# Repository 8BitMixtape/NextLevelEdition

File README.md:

NextLevelEdition
================

SMD 32U4 Massproduction Ready PCB that fits in Mixtape

How to install
================
Download Hardware Cores from Sparkfun:
https://learn.sparkfun.com/tutorials/pro-micro--fio-v3-hookup-guide/installing-mac--linux

For Linux udev rules needs to be changed:
http://forum.arduino.cc/index.php?topic=217910.0

```
/etc/udev/rules.d/70-persistent-net.rules

 # 8Bit Mixtape NextLevel Shit
 
ATTRS{idVendor}=="1b4f", ATTRS{idProduct}=="f100", ENV{ID_MM_DEVICE_IGNORE}="1"

ATTRS{idVendor}=="1b4f", ATTRS{idProduct}=="f101", ENV{ID_MM_DEVICE_IGNORE}="1"
```

Troubleshooting
================

If the serial port doesn't appear, see above.

Strange blinking: Did you attach the LiPo battery?

Bricked the board? if you choose the wrong board and upload this might happen. solder on the ISP plug and burn the bootloader. the files is in the core.

for linux:
`avrdude -P /dev/ttyACM0 -b 19200 -c avrisp -p m32u4 -v -e -U flash:w:Caterina-fio.hex:i`

Pins:
================

2 x Analog Input
----------------
A0 ( you can also only write 0) -> D18

A1 ( you can also only write 1) -> D19

2 x Digital Input / Buttons
---------------------------
D2 (2)

D3 (3)

Sound Output
------------
D9 (9) also connected to LED2

LEDs
----
D13 (13)

the middle i don't know. maybe charge state?

RX (0)

TX (1)

Timers
============

To change the prescaler of the timer connected to Pin9 (sound output)

```
TCCR1B = TCCR0B & 0b11111001; //no timer pre-scaler, fast PWM
```

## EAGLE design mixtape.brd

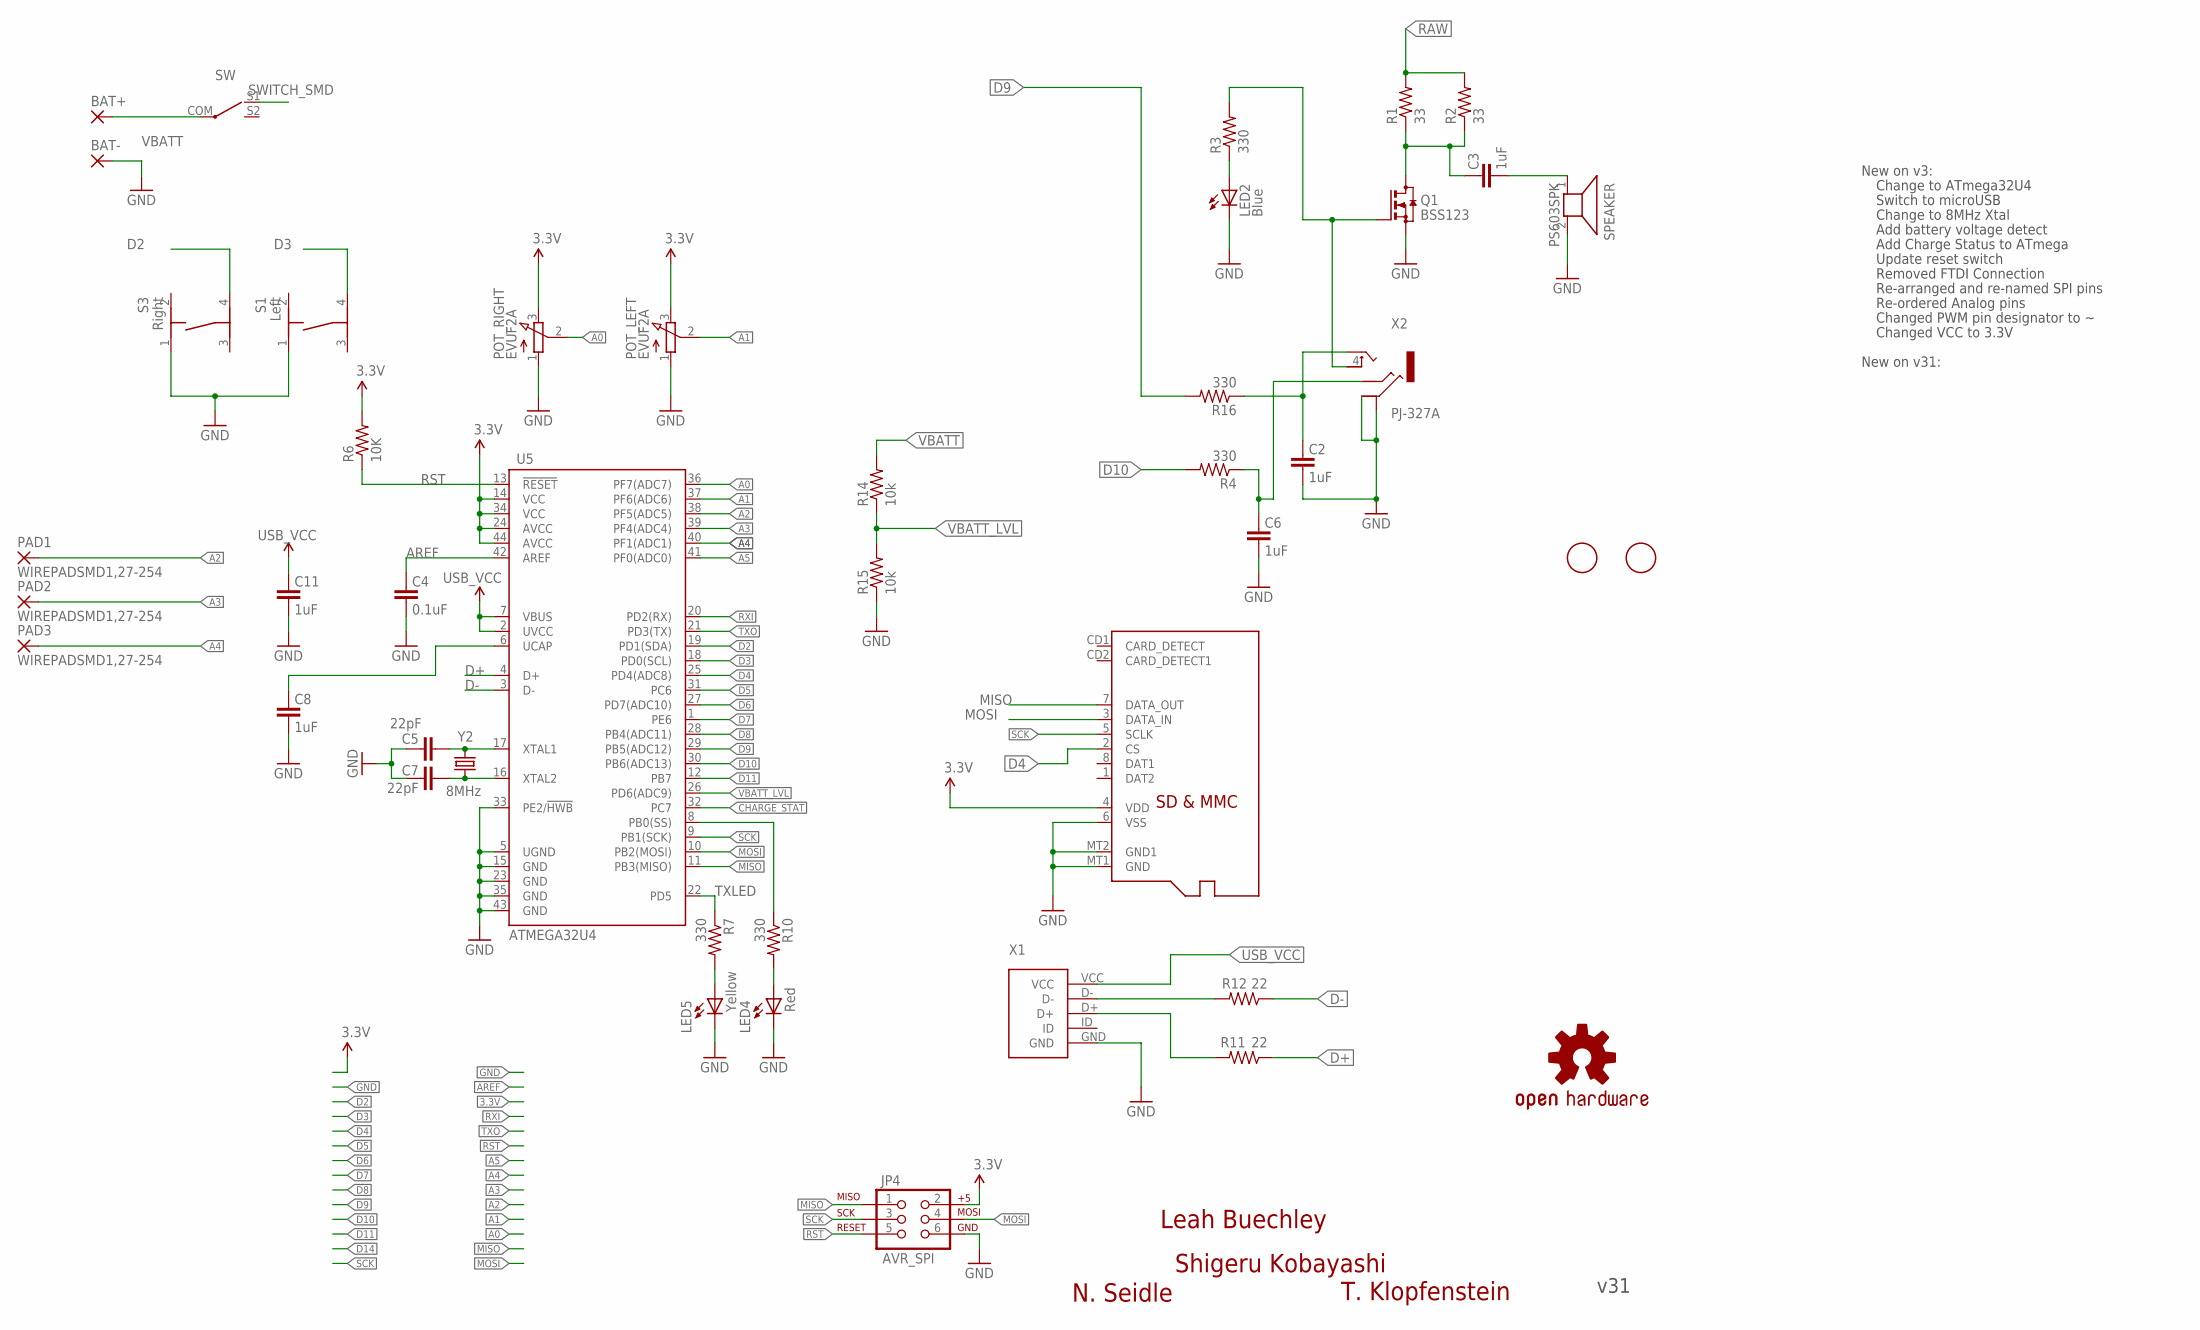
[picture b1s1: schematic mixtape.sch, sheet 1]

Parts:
BAT+: SMD5; SMD2,54-5,08
BAT-: SMD5; SMD2,54-5,08
C2, C3, C6, C8, C11: 1uF; 0603-CAP
C4: 0.1uF; 0603-CAP
C5, C7: 22pF; 0603-CAP
JP4: AVR_SPI; 2X3
LED2: Blue; LED-0603
LED4: Red; LED-0603
LED5: Yellow; LED-0603
LOGO1: OSHW-LOGOL; OSHW-LOGO-L
PAD1, PAD2, PAD3: WIREPADSMD1,27-254; SMD1,27-2,54
POT_LEFT: EVUF2A; EVUF
POT_RIGHT: EVUF2A; EVUF
Q1: BSS123; SOT23
R1, R2: 33; 0603-RES
R3, R4, R7, R10, R16: 330; 0603-RES
R6: 10K; 0603-RES
R11, R12: 22; 0603-RES
R14, R15: 10k; 0603-RES
S1: Left; TASTER-9314_SMD
S3: Right; TASTER-9314_SMD
SD: MICROSD
SPEAKER: PS603SPK; PS603
SW: SWITCH_SMD
U5: ATMEGA32U4; QFN-44-NOPAD_1:1
U$1, U$2: FIDUCIAL; FIDUCIAL_1MM
X1: USB_B_SMD
X2: PJ-327A
Y2: 8MHz; CRYSTAL-SMD-5X3

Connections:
3.3V: JP4.2, POT_LEFT.3 (E), POT_RIGHT.3 (E), R6.2, SD.4 (VDD), U5.14 (VCC), U5.24 (AVCC), U5.34 (VCC), U5.44 (AVCC); also elsewhere on the board
A0: POT_RIGHT.2 (S), U5.36 (PF7(ADC7))
A1: POT_LEFT.2 (S), U5.37 (PF6(ADC6))
A2: PAD1.1, U5.38 (PF5(ADC5))
A3: PAD2.1, U5.39 (PF4(ADC4))
A4: PAD3.1, U5.40 (PF1(ADC1))
A5: U5.41 (PF0(ADC0))
AREF: C4.2, U5.42 (AREF)
CHARGE_STAT: U5.32 (PC7); also elsewhere on the board
D2: S3.4, U5.19 (PD1(SDA))
D3: S1.4, U5.18 (PD0(SCL))
D4: SD.2 (CS), U5.25 (PD4(ADC8))
D5: U5.31 (PC6)
D6: U5.27 (PD7(ADC10))
D7: U5.1 (PE6)
D8: U5.28 (PB4(ADC11))
D9: R16.2, U5.29 (PB5(ADC12))
D10: R4.2, U5.30 (PB6(ADC13))
D11: U5.12 (PB7)
D14: R10.1, U5.8 (PB0(SS))
D+: R11.1, U5.4 (D+)
D-: R12.1, U5.3 (D-)
GND: BAT-.1, C2.1, C4.1, C5.2, C6.1, C7.2, C8.1, C11.1, JP4.6, LED2.C, LED4.C, LED5.C, POT_LEFT.1 (A), POT_RIGHT.1 (A), Q1.2 (S), R15.1, S1.1, S3.1, SD.6 (VSS), SD.MT1 (GND), SD.MT2 (GND1), SPEAKER.2, U5.5 (UGND), U5.15 (GND), U5.23 (GND), U5.33 (PE2/!HWB), U5.35 (GND), U5.43 (GND), X1.GND, X2.1, X2.5; also elsewhere on the board
MISO: JP4.1, SD.7 (DATA_OUT), U5.11 (PB3(MISO))
MOSI: JP4.4, SD.3 (DATA_IN), U5.10 (PB2(MOSI))
unnamed: C3.2, Q1.3 (D), R1.1, R2.1
unnamed: C3.1, SPEAKER.1
unnamed: C6.2, R4.1, X2.3
unnamed: R11.2, X1.D+
unnamed: LED2.A, R3.1
unnamed: Q1.1 (G), R3.2, X2.4
unnamed: LED5.A, R7.2
unnamed: C7.1, U5.16 (XTAL2), Y2.1
unnamed: C5.1, U5.17 (XTAL1), Y2.3 (2)
unnamed: LED4.A, R10.2
unnamed: R12.2, X1.D-
unnamed: C2.2, R16.1, X2.2
RAW: R1.2, R2.2, SW.S1; also elsewhere on the board
RST: JP4.5, R6.1, U5.13 (!RESET)
RXI: U5.20 (PD2(RX))
SCK: JP4.3, SD.5 (SCLK), U5.9 (PB1(SCK))
TXLED: R7.1, U5.22 (PD5)
TXO: U5.21 (PD3(TX))
UCAP: C8.2, U5.6 (UCAP)
USB_VCC: C11.2, U5.2 (UVCC), U5.7 (VBUS), X1.VCC; also elsewhere on the board
VBATT: BAT+.1, R14.2, SW.COM; also elsewhere on the board
VBATT_LVL: R14.1, R15.2, U5.26 (PD6(ADC9))

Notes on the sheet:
Shigeru Kobayashi
Change to ATmega32U4
Switch to microUSB
New on v3:
Change to 8MHz Xtal
Add battery voltage detect
Add Charge Status to ATmega
Update reset switch
Removed FTDI Connection
Re-arranged and re-named SPI pins
Re-ordered Analog pins
Changed PWM pin designator to ~
Changed VCC to 3.3V
New on v31:
v31
N. Seidle
T. Klopfenstein
Leah Buechley

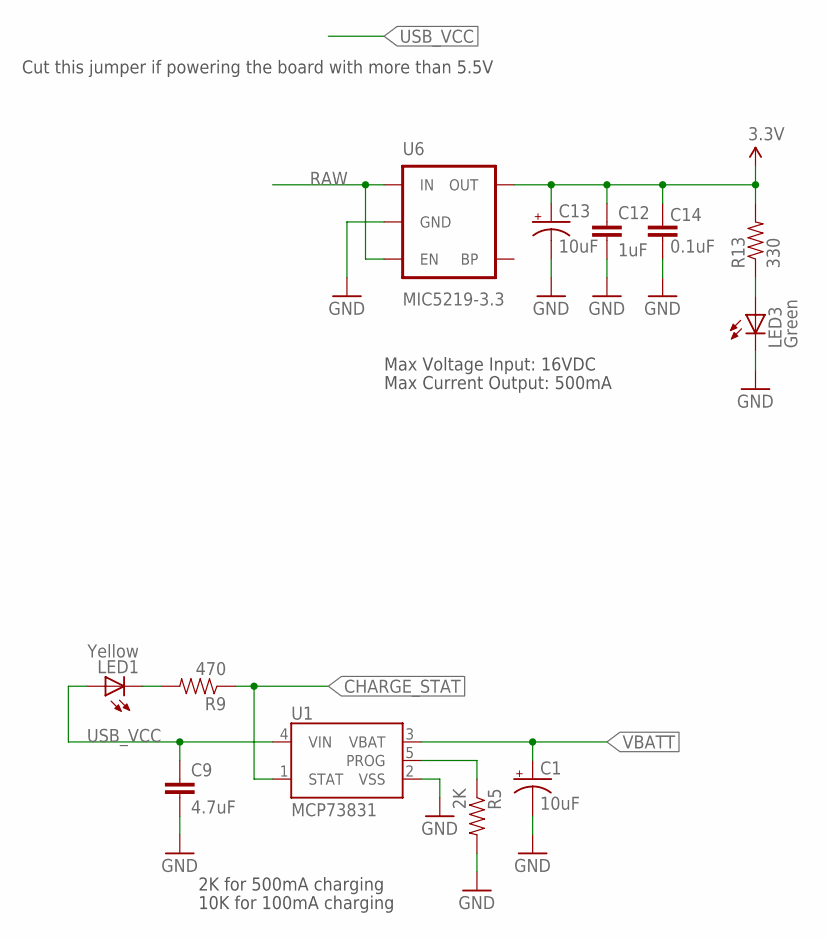
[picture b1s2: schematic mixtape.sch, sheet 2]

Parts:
C1, C13: 10uF; EIA3216
C9: 4.7uF; 0603-CAP
C12: 1uF; 0603-CAP
C14: 0.1uF; 0603-CAP
LED1: Yellow; LED-0603
LED3: Green; LED-0603
R5: 2K; 0603-RES
R9: 470; 0603-RES
R13: 330; 0603-RES
U1: MCP73831; SOT23-5
U6: MIC5219-3.3; SOT23-5

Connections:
3.3V: C12.1, C13.A (+), C14.2, R13.2, U6.5 (OUT); also elsewhere on the board
CHARGE_STAT: R9.1, U1.1 (STAT); also elsewhere on the board
GND: C1.C (-), C9.2, C12.2, C13.C (-), C14.1, LED3.C, R5.2, U1.2 (VSS), U6.2 (GND); also elsewhere on the board
unnamed: LED1.C, R9.2
unnamed: R5.1, U1.5 (PROG)
unnamed: LED3.A, R13.1
RAW: U6.1 (IN), U6.3 (EN); also elsewhere on the board
USB_VCC: C9.1, LED1.A, U1.4 (VIN); also elsewhere on the board
VBATT: C1.A (+), U1.3 (VBAT); also elsewhere on the board

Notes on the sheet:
Max Voltage Input: 16VDC
Max Current Output: 500mA
Cut this jumper if powering the board with more than 5.5V
2K for 500mA charging
10K for 100mA charging

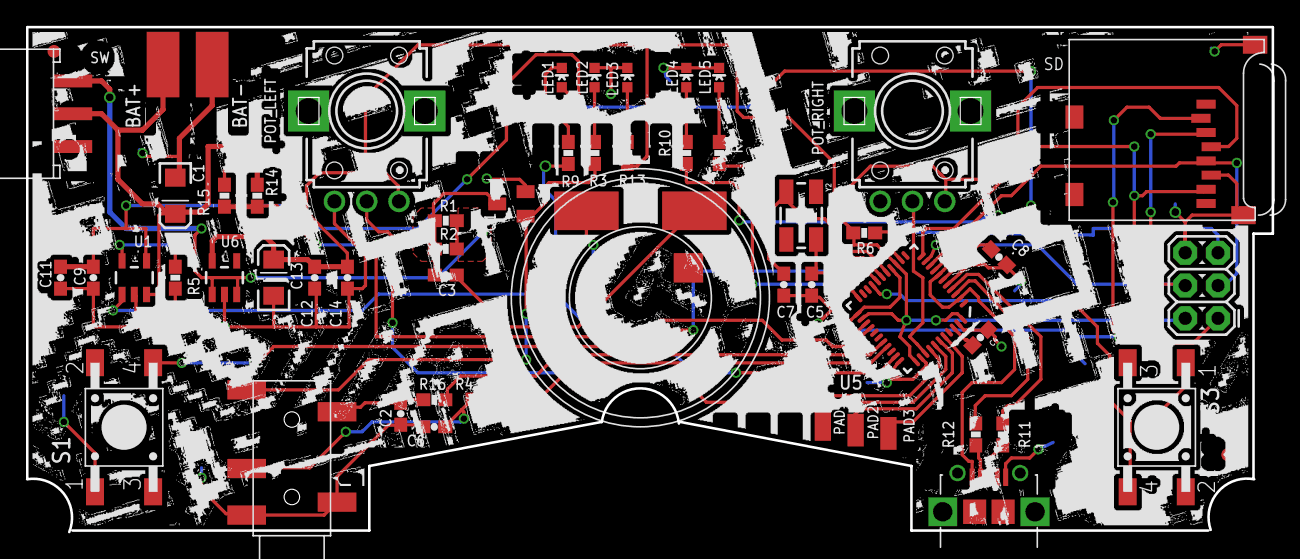
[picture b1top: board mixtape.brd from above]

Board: 4 copper layers, 96.5 x 39.1 mm, 57 parts (1 on the bottom side), 42 nets.

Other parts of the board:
U$4: FIO_LOGOV2; FUNNEL_LOGO_BOTTOM_V2

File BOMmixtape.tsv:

References	Qty	Description	Mouser	Farnell
U1	1	MCP73831	579-MCP73831T-2ATIOT	1840935
U5	1	ATMEGA32U4	556-ATMEGA32U4-MU 	2425127
U6	1	MIC5219-3.3	998-MIC5219-3.3YM5TR	2510252RL
Q1	1	BSS123	512-BSS123	9845321
Y2	1	8MHz	717-7B-8.000MAAJ-T 	2308726
C1, C13	2	10uF	81-GRM31CR71A106KA01	
C2,C3,C6,C8,C11,C12	6	1uF	81-GRM188R61E105KA12	
C4, C14	2	0.1uF	81-GRM39X104K50D	
C5, C7	2	22pF	81-GRM39C220J50	
C9	1	4.7uF	81-GRM18R60J475KE19D 	
LED1	1	Yellow	859-LTST-C190KSKT	
LED2	1	Red	859-LTST-C190KGKT	
LED3	1	Red	859-LTST-C190KGKT	
LED4	1	Blue	859-LTST-C190TBKT	
LED5	1	Yellow	859-LTST-C190KSKT	
R1, R2	2	33	667-ERJ-3GEYJ330V	
R3, R4, R7, R10, R13, R16	6	330	667-ERJ-3GEYJ331V	
R5	1	2K	667-ERJ-3GEYJ222V	
R6, R14, R15	3	10K	667-ERJ-3GEYJ103V	
R9	1	470	667-ERJ-3GEYJ470V	
R11, R12	2	22	667-ERJ-3GEYJ220V	
POT_LEFT	1		652-PTV09A-4015UB103	
POT_RIGHT	1		652-PTV09A-4015UB103	
S1	1	Left	693-1301.9317	1217767
S3	1	Right	693-1301.9317	1217767
SW	1	SWITCH_SMD, SS SMD402, reichelt.de		
SD	1	MICROSD	710-693071010811	2081363
SPEAKER	1	PS603SPK	665-AS01508MRR	
X1	1	USB_B_SMD	649-10118192-0001LF	2506104
X2	1	PJ-327A, ebay		
Accu	1	AKKU IPD SH 1G, reichelt.de

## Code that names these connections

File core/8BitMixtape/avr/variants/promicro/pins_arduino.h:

/*
  pins_arduino.h - Pin definition functions for Arduino
  Part of Arduino - http://www.arduino.cc/

  Copyright (c) 2007 David A. Mellis

  This library is free software; you can redistribute it and/or
  modify it under the terms of the GNU Lesser General Public
  License as published by the Free Software Foundation; either
  version 2.1 of the License, or (at your option) any later version.

  This library is distributed in the hope that it will be useful,
  but WITHOUT ANY WARRANTY; without even the implied warranty of
  MERCHANTABILITY or FITNESS FOR A PARTICULAR PURPOSE.  See the GNU
  Lesser General Public License for more details.

  You should have received a copy of the GNU Lesser General
  Public License along with this library; if not, write to the
  Free Software Foundation, Inc., 59 Temple Place, Suite 330,
  Boston, MA  02111-1307  USA

  $Id: wiring.h 249 2007-02-03 16:52:51Z mellis $
*/

#ifndef Pins_Arduino_h
#define Pins_Arduino_h

#include <avr/pgmspace.h>

#define TX_RX_LED_INIT	DDRD |= (1<<5), DDRB |= (1<<0)
#define TXLED0			PORTD |= (1<<5)
#define TXLED1			PORTD &= ~(1<<5)
#define RXLED0			PORTB |= (1<<0)
#define RXLED1			PORTB &= ~(1<<0)

#define NUM_ANALOG_INPUTS 12

static const uint8_t SDA = 2;
static const uint8_t SCL = 3;

// Map SPI port to 'new' pins D14..D17
static const uint8_t SS   = 17;
static const uint8_t MOSI = 16;
static const uint8_t MISO = 14;
static const uint8_t SCK  = 15;

// Mapping of analog pins as digital I/O
// A6-A11 share with digital pins
static const uint8_t A0 = 18;
static const uint8_t A1 = 19;
static const uint8_t A2 = 20;
static const uint8_t A3 = 21;
static const uint8_t A4 = 22;
static const uint8_t A5 = 23;
static const uint8_t A6 = 24;	// D4
static const uint8_t A7 = 25;	// D6
static const uint8_t A8 = 26;	// D8
static const uint8_t A9 = 27;	// D9
static const uint8_t A10 = 28;	// D10
static const uint8_t A11 = 29;	// D12

#define digitalPinToPCICR(p)    ((((p) >= 8 && (p) <= 11) || ((p) >= 14 && (p) <= 17) || ((p) >= A8 && (p) <= A10)) ? (&PCICR) : ((uint8_t *)0))
#define digitalPinToPCICRbit(p) 0
#define digitalPinToPCMSK(p)    ((((p) >= 8 && (p) <= 11) || ((p) >= 14 && (p) <= 17) || ((p) >= A8 && (p) <= A10)) ? (&PCMSK0) : ((uint8_t *)0))
#define digitalPinToPCMSKbit(p) ( ((p) >= 8 && (p) <= 11) ? (p) - 4 : ((p) == 14 ? 3 : ((p) == 15 ? 1 : ((p) == 16 ? 2 : ((p) == 17 ? 0 : (p - A8 + 4))))))

//	__AVR_ATmega32U4__ has an unusual mapping of pins to channels
extern const uint8_t PROGMEM analog_pin_to_channel_PGM[];
#define analogPinToChannel(P)  ( pgm_read_byte( analog_pin_to_channel_PGM + (P) ) )

#ifdef ARDUINO_MAIN

// On the Arduino board, digital pins are also used
// for the analog output (software PWM).  Analog input
// pins are a separate set.

// ATMEL ATMEGA32U4 / ARDUINO LEONARDO
//
// D0				PD2					RXD1/INT2
// D1				PD3					TXD1/INT3
// D2				PD1		SDA			SDA/INT1
// D3#				PD0		PWM8/SCL	OC0B/SCL/INT0
// D4		A6		PD4					ADC8
// D5#				PC6		???			OC3A/#OC4A
// D6#		A7		PD7		FastPWM		#OC4D/ADC10
// D7				PE6					INT6/AIN0
//
// D8		A8		PB4					ADC11/PCINT4
// D9#		A9		PB5		PWM16		OC1A/#OC4B/ADC12/PCINT5
// D10#		A10		PB6		PWM16		OC1B/0c4B/ADC13/PCINT6
// D11#				PB7		PWM8/16		0C0A/OC1C/#RTS/PCINT7
// D12		A11		PD6					T1/#OC4D/ADC9
// D13#				PC7		PWM10		CLK0/OC4A
//
// A0		D18		PF7					ADC7
// A1		D19		PF6					ADC6
// A2		D20 	PF5					ADC5
// A3		D21 	PF4					ADC4
// A4		D22		PF1					ADC1
// A5		D23 	PF0					ADC0
//
// New pins D14..D17 to map SPI port to digital pins
//
// MISO		D14		PB3					MISO,PCINT3
// SCK		D15		PB1					SCK,PCINT1
// MOSI		D16		PB2					MOSI,PCINT2
// SS		D17		PB0					RXLED,SS/PCINT0
//
// TXLED			PD5
// RXLED		    PB0
// HWB				PE2					HWB

// these arrays map port names (e.g. port B) to the
// appropriate addresses for various functions (e.g. reading
// and writing)
const uint16_t PROGMEM port_to_mode_PGM[] = {
	NOT_A_PORT,
	NOT_A_PORT,
	(uint16_t) &DDRB,
	(uint16_t) &DDRC,
	(uint16_t) &DDRD,
	(uint16_t) &DDRE,
	(uint16_t) &DDRF,
};

const uint16_t PROGMEM port_to_output_PGM[] = {
	NOT_A_PORT,
	NOT_A_PORT,
	(uint16_t) &PORTB,
	(uint16_t) &PORTC,
	(uint16_t) &PORTD,
	(uint16_t) &PORTE,
	(uint16_t) &PORTF,
};

const uint16_t PROGMEM port_to_input_PGM[] = {
	NOT_A_PORT,
	NOT_A_PORT,
	(uint16_t) &PINB,
	(uint16_t) &PINC,
	(uint16_t) &PIND,
	(uint16_t) &PINE,
	(uint16_t) &PINF,
};

const uint8_t PROGMEM digital_pin_to_port_PGM[30] = {
	PD, // D0 - PD2
	PD,	// D1 - PD3
	PD, // D2 - PD1
	PD,	// D3 - PD0
	PD,	// D4 - PD4
	PC, // D5 - PC6
	PD, // D6 - PD7
	PE, // D7 - PE6
	
	PB, // D8 - PB4
	PB,	// D9 - PB5
	PB, // D10 - PB6
	PB,	// D11 - PB7
	PD, // D12 - PD6
	PC, // D13 - PC7
	
	PB,	// D14 - MISO - PB3
	PB,	// D15 - SCK - PB1
	PB,	// D16 - MOSI - PB2
	PB,	// D17 - SS - PB0
	
	PF,	// D18 - A0 - PF7
	PF, // D19 - A1 - PF6
	PF, // D20 - A2 - PF5
	PF, // D21 - A3 - PF4
	PF, // D22 - A4 - PF1
	PF, // D23 - A5 - PF0
	
	PD, // D24 / D4 - A6 - PD4
	PD, // D25 / D6 - A7 - PD7
	PB, // D26 / D8 - A8 - PB4
	PB, // D27 / D9 - A9 - PB5
	PB, // D28 / D10 - A10 - PB6
	PD, // D29 / D12 - A11 - PD6
};

const uint8_t PROGMEM digital_pin_to_bit_mask_PGM[30] = {
	_BV(2), // D0 - PD2
	_BV(3),	// D1 - PD3
	_BV(1), // D2 - PD1
	_BV(0),	// D3 - PD0
	_BV(4),	// D4 - PD4
	_BV(6), // D5 - PC6
	_BV(7), // D6 - PD7
	_BV(6), // D7 - PE6
	
	_BV(4), // D8 - PB4
	_BV(5),	// D9 - PB5
	_BV(6), // D10 - PB6
	_BV(7),	// D11 - PB7
	_BV(6), // D12 - PD6
	_BV(7), // D13 - PC7
	
	_BV(3),	// D14 - MISO - PB3
	_BV(1),	// D15 - SCK - PB1
	_BV(2),	// D16 - MOSI - PB2
	_BV(0),	// D17 - SS - PB0
	
	_BV(7),	// D18 - A0 - PF7
	_BV(6), // D19 - A1 - PF6
	_BV(5), // D20 - A2 - PF5
	_BV(4), // D21 - A3 - PF4
	_BV(1), // D22 - A4 - PF1
	_BV(0), // D23 - A5 - PF0
	
	_BV(4), // D24 / D4 - A6 - PD4
	_BV(7), // D25 / D6 - A7 - PD7
	_BV(4), // D26 / D8 - A8 - PB4
	_BV(5), // D27 / D9 - A9 - PB5
	_BV(6), // D28 / D10 - A10 - PB6
	_BV(6), // D29 / D12 - A11 - PD6
};

const uint8_t PROGMEM digital_pin_to_timer_PGM[16] = {
	NOT_ON_TIMER,	
	NOT_ON_TIMER,
	NOT_ON_TIMER,
	TIMER0B,		/* 3 */
	NOT_ON_TIMER,
	TIMER3A,		/* 5 */
	TIMER4D,		/* 6 */
	NOT_ON_TIMER,	
	
	NOT_ON_TIMER,	
	TIMER1A,		/* 9 */
	TIMER1B,		/* 10 */
	TIMER0A,		/* 11 */
	
	NOT_ON_TIMER,	
	TIMER4A,		/* 13 */
	
	NOT_ON_TIMER,	
	NOT_ON_TIMER,
};

const uint8_t PROGMEM analog_pin_to_channel_PGM[12] = {
	7,	// A0				PF7					ADC7
	6,	// A1				PF6					ADC6	
	5,	// A2				PF5					ADC5	
	4,	// A3				PF4					ADC4
	1,	// A4				PF1					ADC1	
	0,	// A5				PF0					ADC0	
	8,	// A6		D4		PD4					ADC8
	10,	// A7		D6		PD7					ADC10
	11,	// A8		D8		PB4					ADC11
	12,	// A9		D9		PB5					ADC12
	13,	// A10		D10		PB6					ADC13
	9	// A11		D12		PD6					ADC9
};

#endif /* ARDUINO_MAIN */
#endif /* Pins_Arduino_h */

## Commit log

2014-12-04 V0.1 PCB Layout
2014-12-04 V 0.11 now with SD card slot
2014-12-09 Finished Routing
2015-01-08 First prototype version, with artwork
2015-01-08 Old files deleted
2015-03-26 4 Song example added
2015-03-26 added modified sparkfun core
2015-03-27 to do list
2015-03-27 fixed pins_arduino.h - Now Mozzi works!
2015-03-27 how to burn new bootloader after bricking
2016-07-21 Production Verions
    Added repot to https://kitnic.it/ with 1-click BOM
2016-07-25 Added Website
2016-08-13 Align board edge curve points with line points
2016-08-13 Add code blocks to README
2016-08-13 Specify format in drill file
2016-08-19 corected error on USB port in BOM
    plus minor updates
2016-08-19 Changed BOM
2016-08-31 Added code folder
    with primary code for the musci player
2016-08-31 Moved old 8Bit code in the code folder
    Not sure that old code is still working...
2017-01-29 added OpenLinerCompilation

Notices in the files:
parts and their libraries:
SparkFun-Capacitors: Licensing: CC v3.0 Share-Alike You are welcome to use this library for commercial purposes.
